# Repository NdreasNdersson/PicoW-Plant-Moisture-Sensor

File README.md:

# Install pre-commit
```
pip install pre-commit
pre-commit install
```

# Build
Following script will build the bootloader and rest sensor board application and combine these as a .bin file. It will
also prepend hash to application so it will be launched by the bootloader.
```
./build_and_combine.sh
```

# Flash first time
Connect Pico Probe and run ./flash_combined.sh

This will flash bootloader, default app info/storage and app.

# Config
Enter wifi SSID and password over serial when promted. Once it have connected, the sensors can be configured with REST API.
```
POST /SENSORS HTTP/1.1
Host: 192.168.X.X
Content-Type: application/json
Content-Length: 147

{"config":[{"calibrate_max_value":false,"calibrate_min_value":false,"inversed":true,"max":17736,"min":8266,"pin":1,"type":"moisture"},{"calibrate_max_value":false,"calibrate_min_value":true,"inversed":true,"max":16509,"min":1,"pin":2,"type":"moisture"}]}
```

# Rest get
Get sensor readings:
```
GET /SENSORS HTTP/1.1
Host: 192.168.50.205
```

Get current sensor config:
```
GET /CONFIG HTTP/1.1
Host: 192.168.50.205
```

# SW download
Run
```
./python/upload_new_binary.py --host 192.168.X.X --app-file build/ninja-release/PICO_REST_SENSOR_STRIPPED.bin
```

# Raspberry Pi Pico W Analog sensor board

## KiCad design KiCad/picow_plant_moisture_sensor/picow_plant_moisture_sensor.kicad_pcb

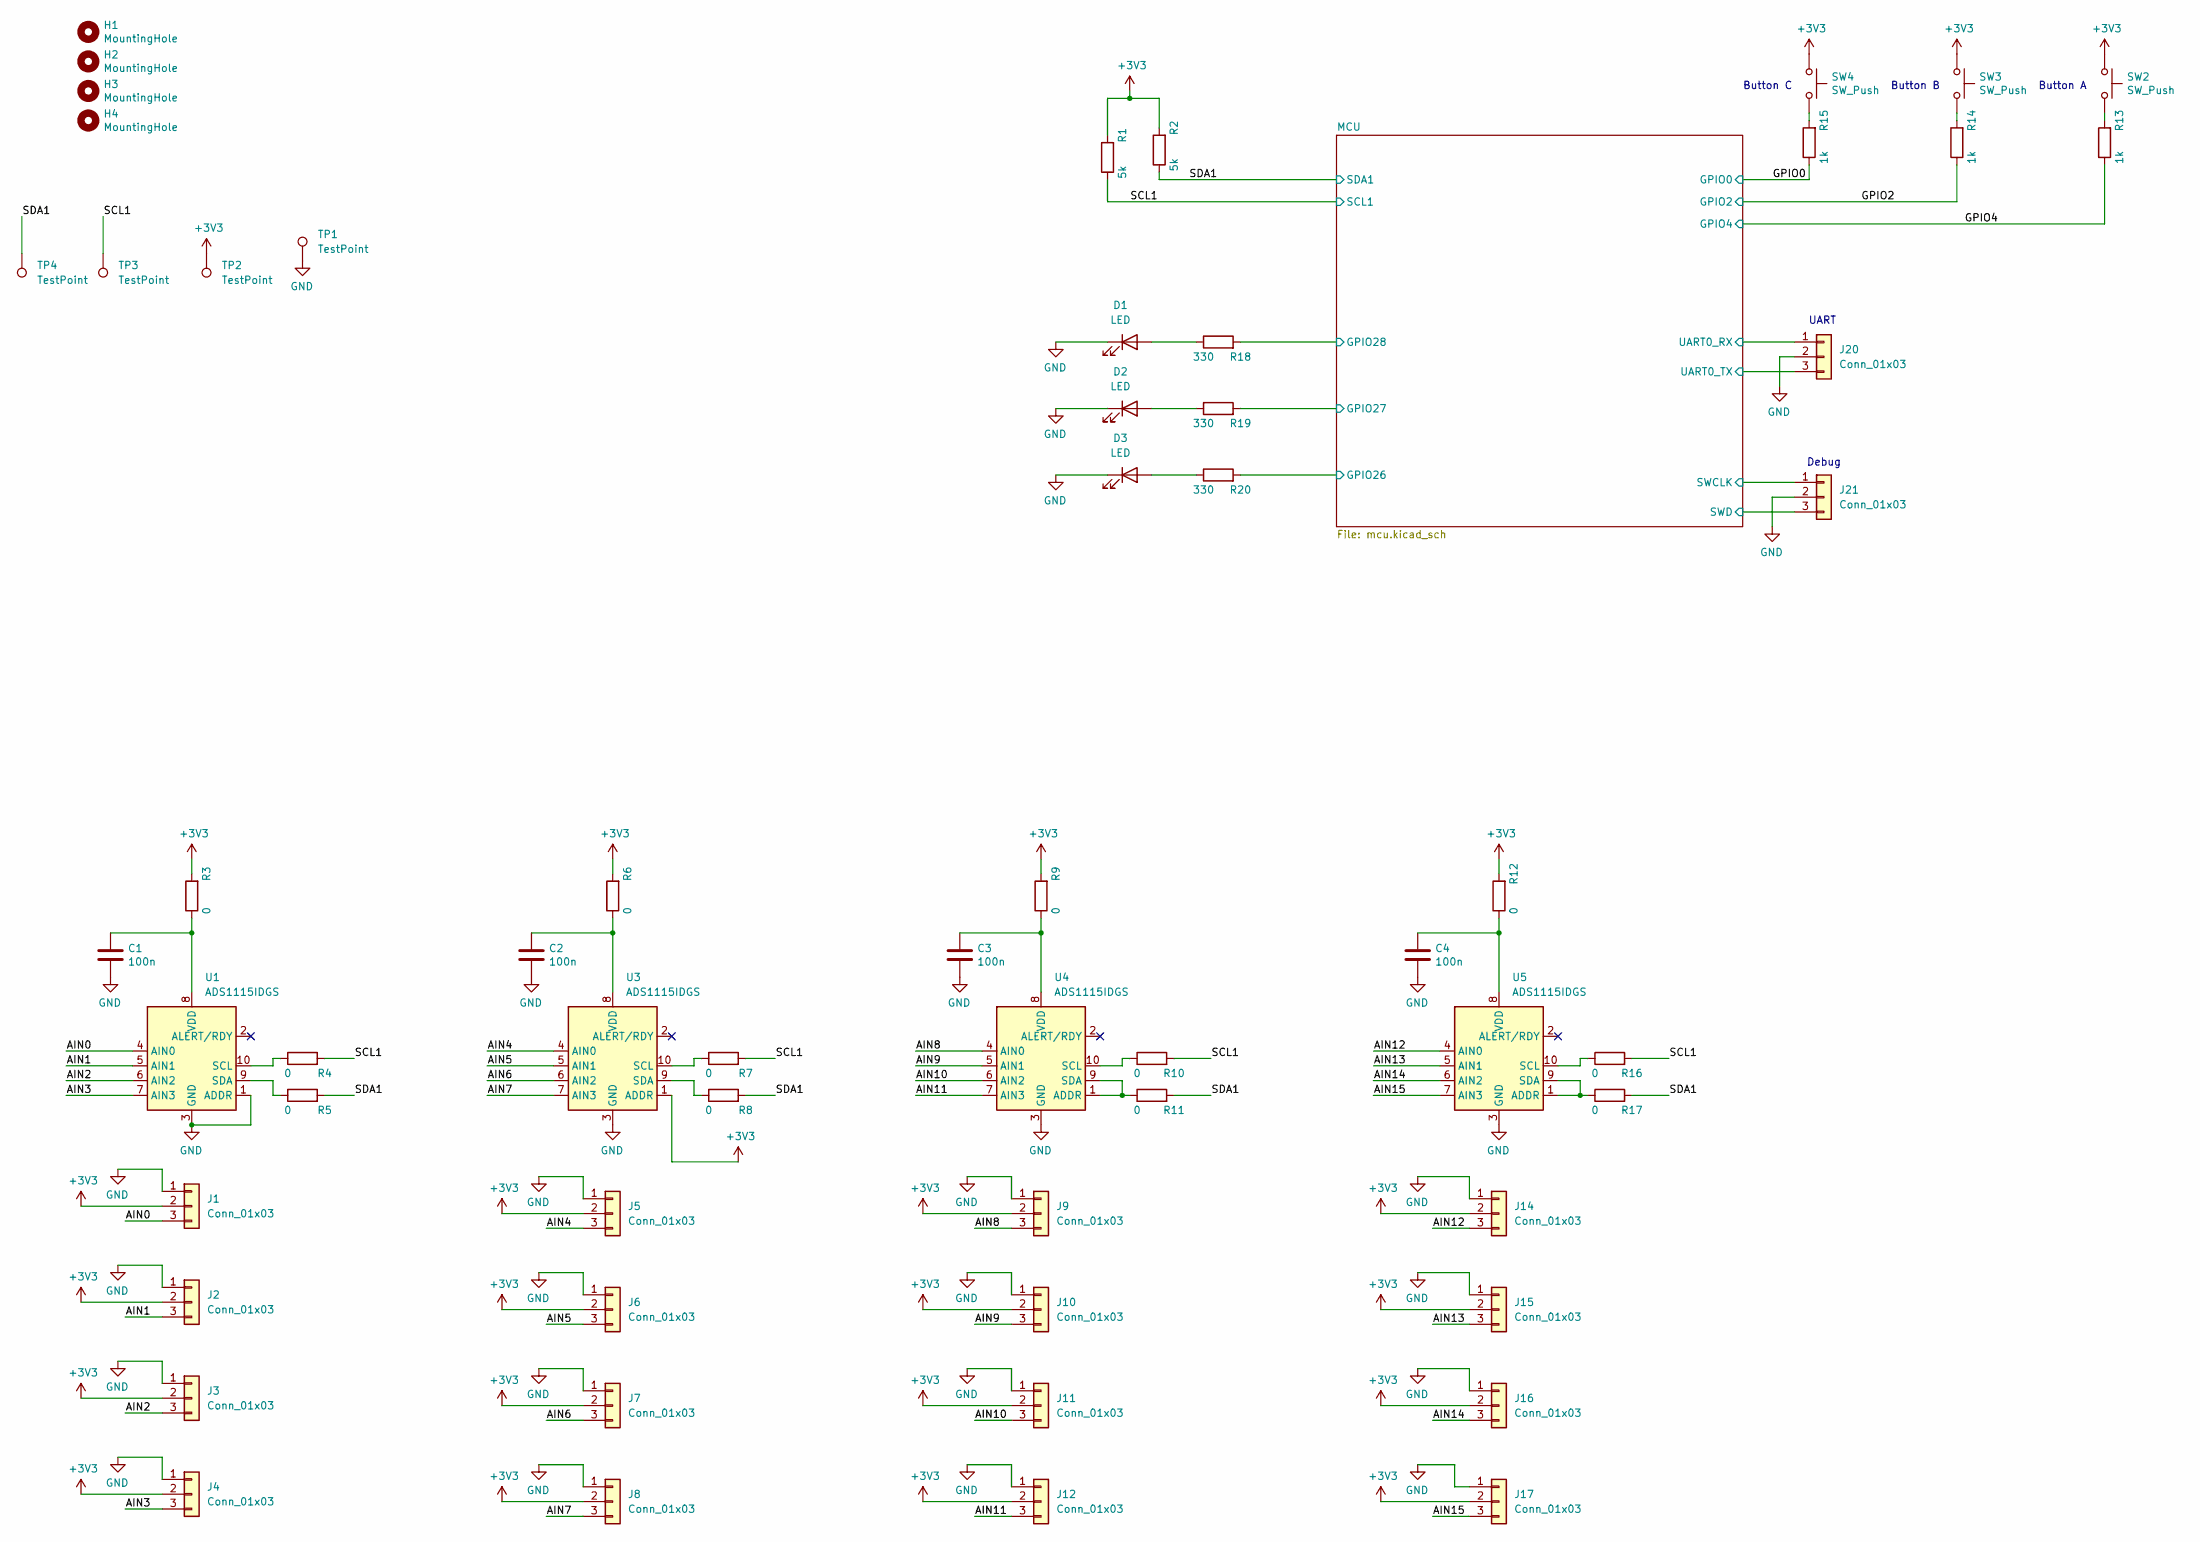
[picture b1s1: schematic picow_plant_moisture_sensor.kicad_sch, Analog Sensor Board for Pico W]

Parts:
C1, C2, C3, C4: 100n; C_0603_1608Metric; LCSC C1525
D1, D2, D3: LED; LED_0603_1608Metric; LCSC C2290
H1, H2, H3, H4: MountingHole; MountingHole_2.7mm_M2.5
J1, J2, J3, J4, J5, J6, J7, J8, J9, J10, J11, J12, J14, J15, J16, J17: Conn_01x03; JST_PH_B3B-PH-K_1x03_P2.00mm_Vertical
J20: Conn_01x03; PinHeader_1x03_P2.54mm_Vertical
J21: Conn_01x03; PinSocket_1x03_P2.54mm_Vertical
R1, R2: 5k; R_0603_1608Metric; LCSC C25900
R3, R4, R5, R6, R7, R8, R9, R10, R11, R12, R16, R17: 0; R_0603_1608Metric; LCSC C21189
R13, R14, R15: 1k; R_0603_1608Metric; LCSC C11702
R18, R19, R20: 330; R_0603_1608Metric; LCSC C25104
SW2, SW3, SW4: SW_Push; SW_SPST_TL3305A
TP1, TP2, TP3, TP4: TestPoint; TestPoint_Pad_D2.0mm
U1, U3, U4, U5: ADS1115IDGS; TSSOP-10_3x3mm_P0.5mm; LCSC C37593

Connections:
+3V3: J1.2, J2.2, J3.2, J4.2, J5.2, J6.2, J7.2, J8.2, J9.2, J10.2, J11.2, J12.2, J14.2, J15.2, J16.2, J17.2, R1.2, R2.2, R3.2, R6.2, R9.2, R12.2, SW2.1, SW3.1, SW4.1, TP2.1, U3.1 (ADDR); also elsewhere on the board
/AIN0: J1.3, U1.4 (AIN0)
/AIN1: J2.3, U1.5 (AIN1)
/AIN2: J3.3, U1.6 (AIN2)
/AIN3: J4.3, U1.7 (AIN3)
/AIN4: J5.3, U3.4 (AIN0)
/AIN5: J6.3, U3.5 (AIN1)
/AIN6: J7.3, U3.6 (AIN2)
/AIN7: J8.3, U3.7 (AIN3)
/AIN8: J9.3, U4.4 (AIN0)
/AIN9: J10.3, U4.5 (AIN1)
/AIN10: J11.3, U4.6 (AIN2)
/AIN11: J12.3, U4.7 (AIN3)
/AIN12: J14.3, U5.4 (AIN0)
/AIN13: J15.3, U5.5 (AIN1)
/AIN14: J16.3, U5.6 (AIN2)
/AIN15: J17.3, U5.7 (AIN3)
/GPIO0: R15.1; also elsewhere on the board
/GPIO2: R14.1; also elsewhere on the board
/GPIO4: R13.1; also elsewhere on the board
/MCU/GPIO26: R20.2; also elsewhere on the board
/MCU/GPIO27: R19.2; also elsewhere on the board
/MCU/GPIO28: R18.2; also elsewhere on the board
/MCU/SWCLK: J21.1; also elsewhere on the board
/MCU/SWD: J21.3; also elsewhere on the board
/MCU/UART0_RX: J20.1; also elsewhere on the board
/MCU/UART0_TX: J20.3; also elsewhere on the board
/SCL1: R1.1, R4.2, R7.2, R10.2, R16.2, TP3.1; also elsewhere on the board
/SDA1: R2.1, R5.2, R8.2, R11.2, R17.2, TP4.1; also elsewhere on the board
GND: C1.2, C2.2, C3.2, C4.2, D1.1 (K), D2.1 (K), D3.1 (K), J1.1, J2.1, J3.1, J4.1, J5.1, J6.1, J7.1, J8.1, J9.1, J10.1, J11.1, J12.1, J14.1, J15.1, J16.1, J17.1, J20.2, J21.2, TP1.1, U1.1 (ADDR), U1.3 (GND), U3.3 (GND), U4.3 (GND), U5.3 (GND); also elsewhere on the board
unnamed: D1.2 (A), R18.1
unnamed: D2.2 (A), R19.1
unnamed: D3.2 (A), R20.1
unnamed: R13.2, SW2.2
unnamed: R14.2, SW3.2
unnamed: R15.2, SW4.2
unnamed: R4.1, U1.10 (SCL)
unnamed: R5.1, U1.9 (SDA)
unnamed: C1.1, R3.1, U1.8 (VDD)
unnamed: R7.1, U3.10 (SCL)
unnamed: R8.1, U3.9 (SDA)
unnamed: C2.1, R6.1, U3.8 (VDD)
unnamed: R11.1, U4.1 (ADDR), U4.9 (SDA)
unnamed: R10.1, U4.10 (SCL)
unnamed: C3.1, R9.1, U4.8 (VDD)
unnamed: R17.1, U5.1 (ADDR), U5.9 (SDA)
unnamed: R16.1, U5.10 (SCL)
unnamed: C4.1, R12.1, U5.8 (VDD)

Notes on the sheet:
Button A
Button B
Button C
UART
Debug

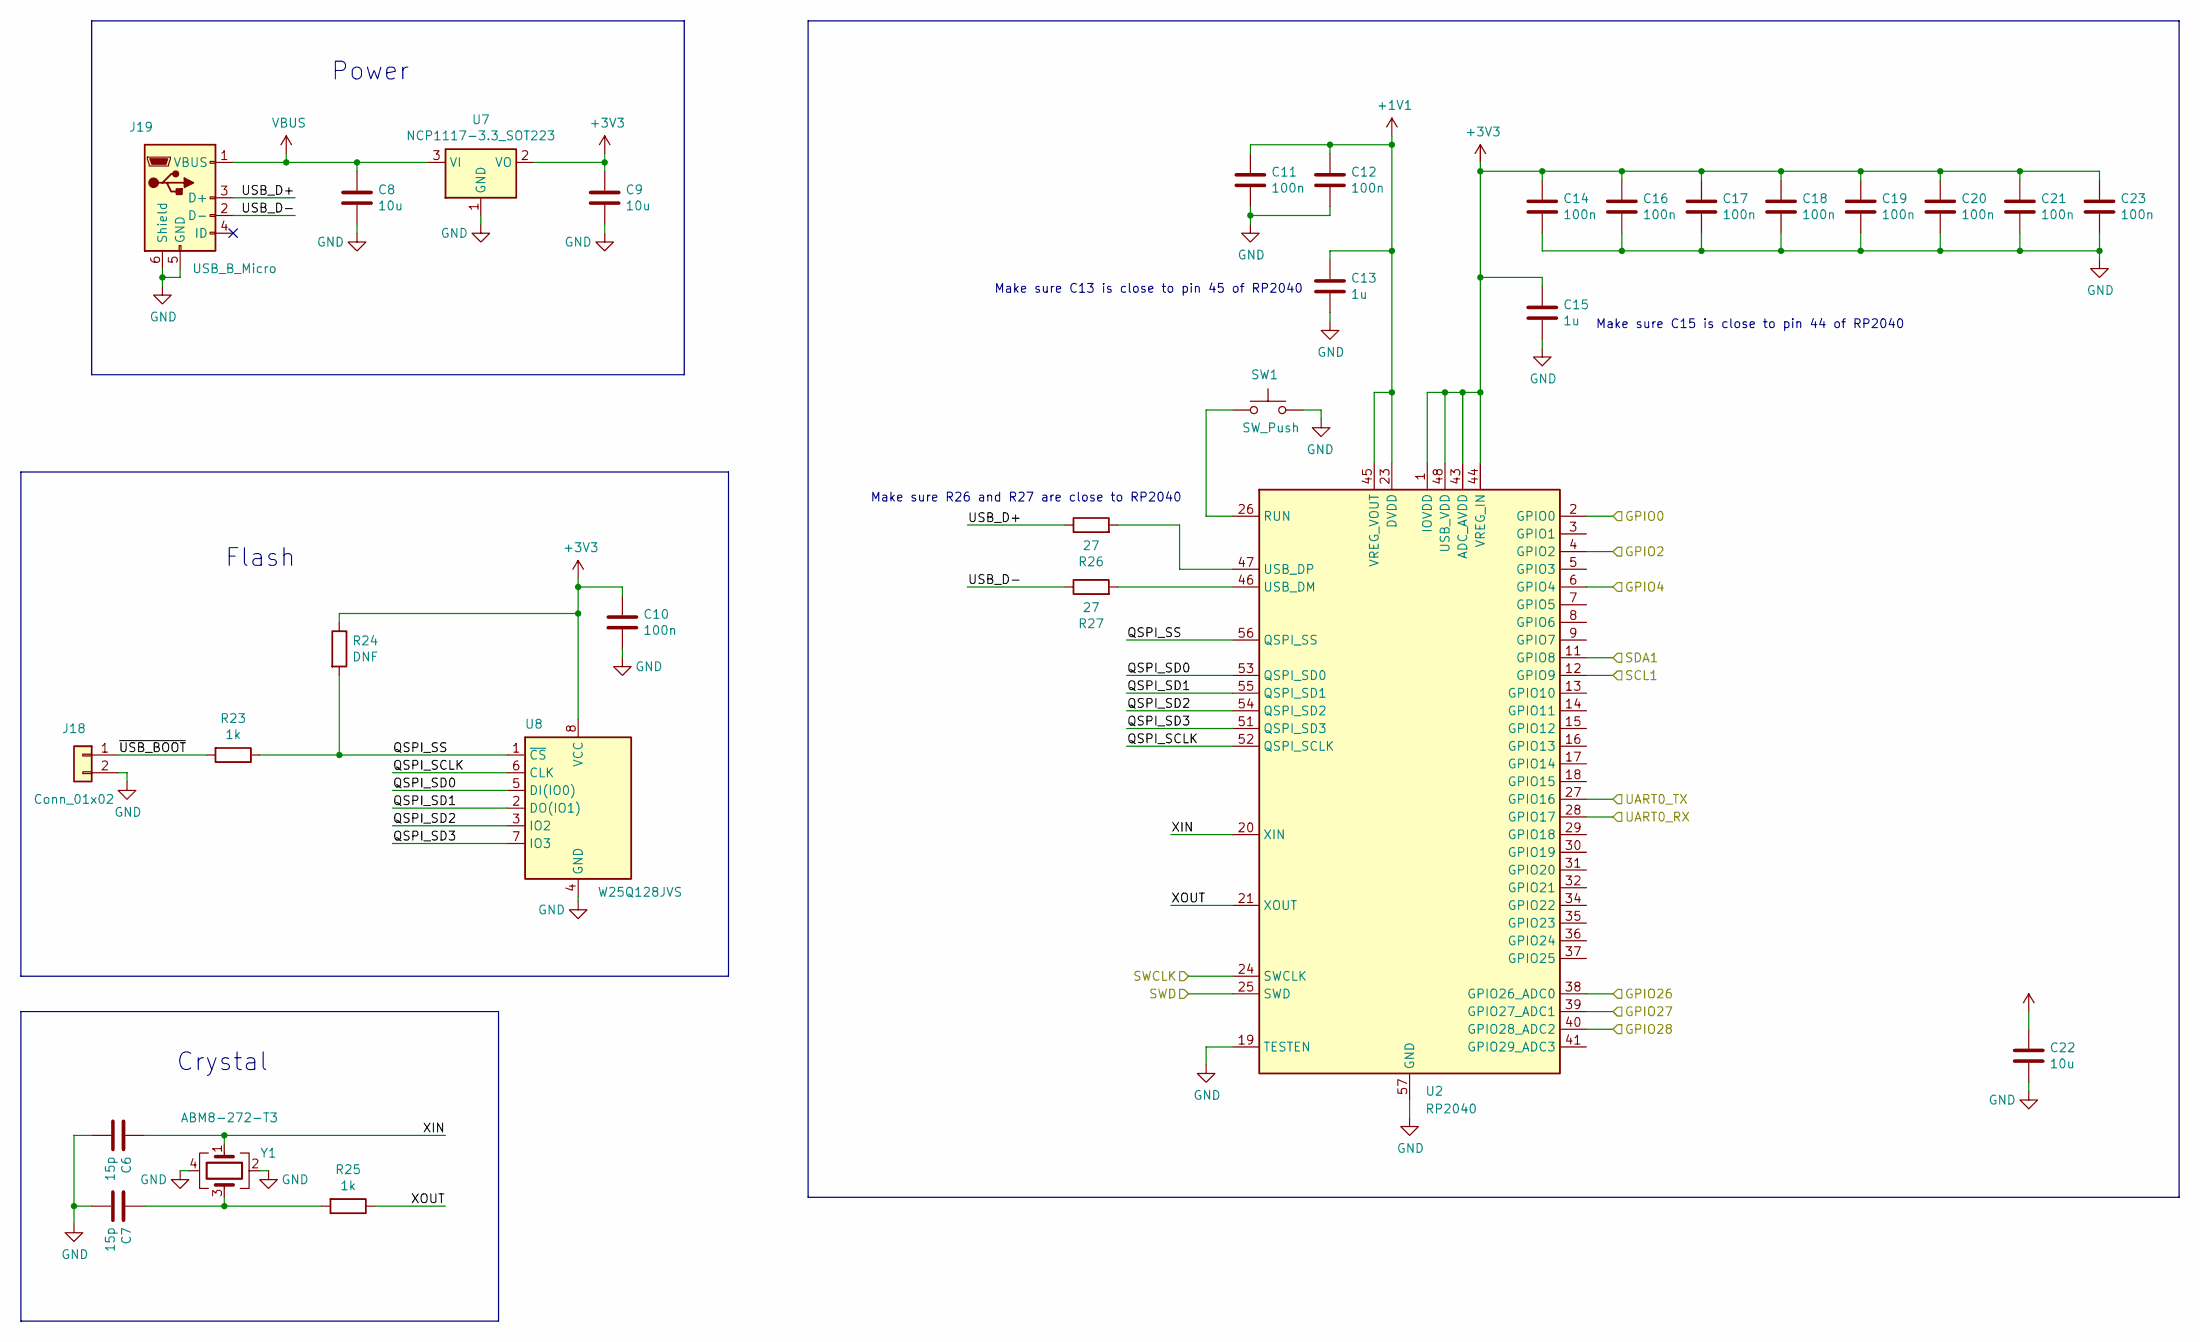
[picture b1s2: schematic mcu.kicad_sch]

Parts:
C6, C7: 15p; C_0402_1005Metric
C8, C9, C22: 10u; C_0805_2012Metric
C10, C11, C12, C14, C16, C17, C18, C19, C20, C21, C23: 100n; C_0402_1005Metric
C13, C15: 1u; C_0402_1005Metric
J18: Conn_01x02; PinHeader_1x02_P2.54mm_Vertical
J19: USB_B_Micro; USB_Micro-B_Amphenol_10103594-0001LF_Horizontal
R23, R25: 1k; R_0402_1005Metric
R24: DNF; R_0402_1005Metric
R26, R27: 27; R_0402_1005Metric
SW1: SW_Push; SW_SPST_TL3305A
U2: RP2040; QFN-56-1EP_7x7mm_P0.4mm_EP3.2x3.2mm
U7: NCP1117-3.3_SOT223; SOT-223-3_TabPin2
U8: W25Q128JVS; SOIC-8_5.23x5.23mm_P1.27mm
Y1: ABM8-272-T3; Crystal_SMD_3225-4Pin_3.2x2.5mm

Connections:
+1V1: C11.1, C12.1, C13.1, U2.23 (DVDD), U2.45 (VREG_VOUT), U2.50 (DVDD)
+3V3: C9.1, C10.1, C14.1, C15.1, C16.1, C17.1, C18.1, C19.1, C20.1, C21.1, C22.1, C23.1, R24.1, U2.1 (IOVDD), U2.10 (IOVDD), U2.22 (IOVDD), U2.33 (IOVDD), U2.42 (IOVDD), U2.43 (ADC_AVDD), U2.44 (VREG_IN), U2.48 (USB_VDD), U2.49 (IOVDD), U7.2 (VO), U8.8 (VCC); also elsewhere on the board
/GPIO0: U2.2 (GPIO0); also elsewhere on the board
/GPIO2: U2.4 (GPIO2); also elsewhere on the board
/GPIO4: U2.6 (GPIO4); also elsewhere on the board
/MCU/GPIO26: U2.38 (GPIO26_ADC0); also elsewhere on the board
/MCU/GPIO27: U2.39 (GPIO27_ADC1); also elsewhere on the board
/MCU/GPIO28: U2.40 (GPIO28_ADC2); also elsewhere on the board
/MCU/QSPI_SCLK: U2.52 (QSPI_SCLK), U8.6 (CLK)
/MCU/QSPI_SD0: U2.53 (QSPI_SD0), U8.5 (DI(IO0))
/MCU/QSPI_SD1: U2.55 (QSPI_SD1), U8.2 (DO(IO1))
/MCU/QSPI_SD2: U2.54 (QSPI_SD2), U8.3 (IO2)
/MCU/QSPI_SD3: U2.51 (QSPI_SD3), U8.7 (IO3)
/MCU/QSPI_SS: R23.1, R24.2, U2.56 (QSPI_SS), U8.1 (~CS)
/MCU/SWCLK: U2.24 (SWCLK); also elsewhere on the board
/MCU/SWD: U2.25 (SWD); also elsewhere on the board
/MCU/UART0_RX: U2.28 (GPIO17); also elsewhere on the board
/MCU/UART0_TX: U2.27 (GPIO16); also elsewhere on the board
/MCU/USB_D+: J19.3 (D+), R26.1
/MCU/USB_D-: J19.2 (D-), R27.1
/MCU/XIN: C6.1, U2.20 (XIN), Y1.1
/MCU/XOUT: R25.1, U2.21 (XOUT)
/MCU/~USB_BOOT: J18.1, R23.2
/SCL1: U2.12 (GPIO9); also elsewhere on the board
/SDA1: U2.11 (GPIO8); also elsewhere on the board
GND: C6.2, C7.2, C8.2, C9.2, C10.2, C11.2, C12.2, C13.2, C14.2, C15.2, C16.2, C17.2, C18.2, C19.2, C20.2, C21.2, C22.2, C23.2, J18.2, J19.5 (GND), J19.6 (Shield), SW1.2, U2.19 (TESTEN), U2.57 (GND), U7.1 (GND), U8.4 (GND), Y1.2, Y1.4; also elsewhere on the board
unnamed: C7.1, R25.2, Y1.3
unnamed: SW1.1, U2.26 (RUN)
unnamed: R27.2, U2.46 (USB_DM)
unnamed: R26.2, U2.47 (USB_DP)
VBUS: C8.1, J19.1 (VBUS), U7.3 (VI)

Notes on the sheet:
Make sure R26 and R27 are close to RP2040
Make sure C13 is close to pin 45 of RP2040
Power
Make sure C15 is close to pin 44 of RP2040
Flash
Crystal

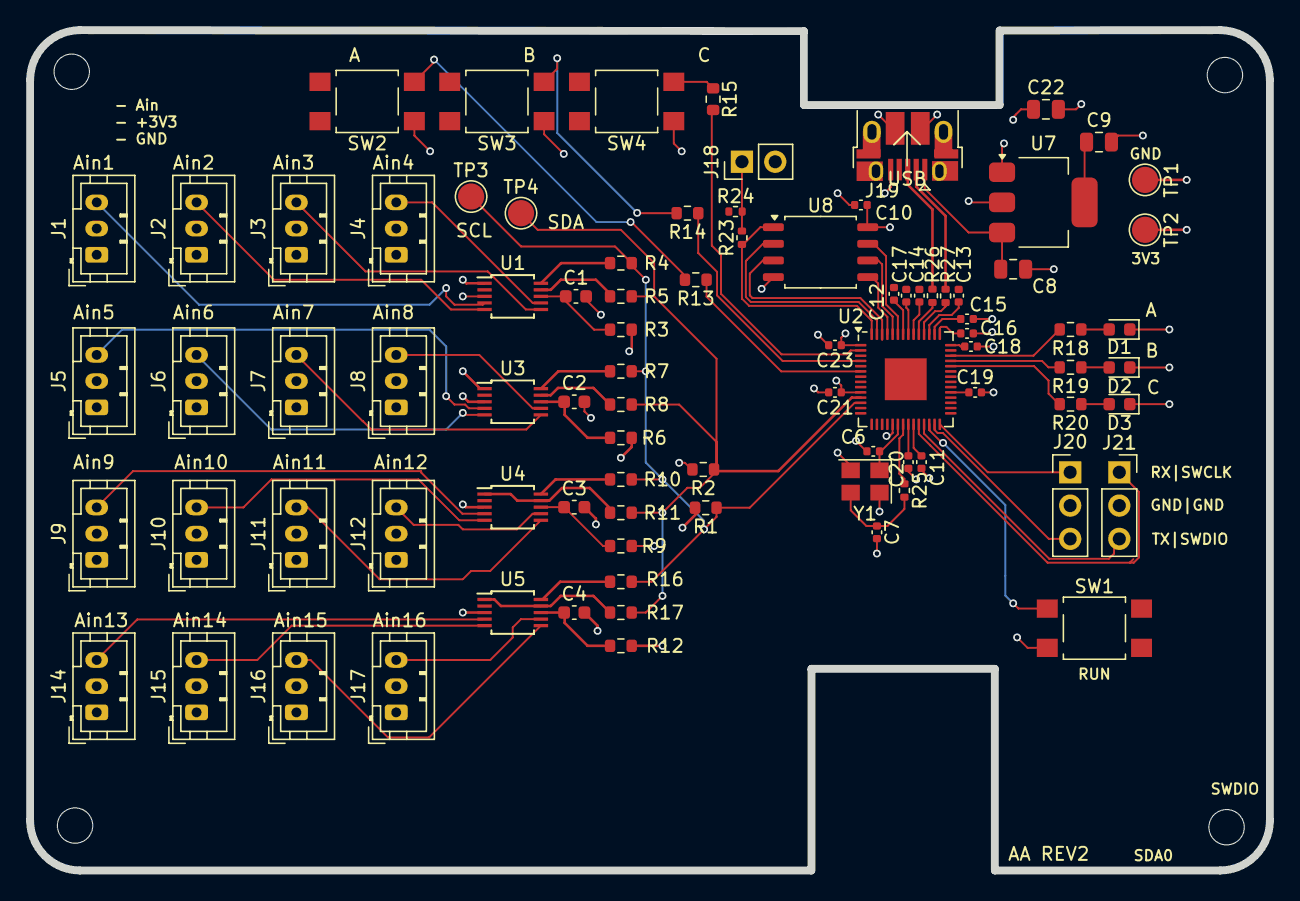
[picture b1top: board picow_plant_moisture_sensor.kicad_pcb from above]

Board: 4 copper layers, 94.6 x 64.1 mm, 90 parts (0 on the bottom side), 65 nets.

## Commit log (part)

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2024-02-03 Restructure files into folders
2024-02-04 Remove TwinThingPicoW include
2024-02-04 Logging with FreeRTOS log interface
2024-02-04 Hangs at MQTT_Connect:2710
2024-02-04 Update MQTT config
2024-02-04 Clean up of things no longer necessary
2024-02-05 TCP working with one buffer to send
2024-02-07 Sending data works
2024-02-07 Rest api (#2)
    * Restructure files into folders
    * Remove TwinThingPicoW include
    * Logging with FreeRTOS log interface
    * Hangs at MQTT_Connect:2710
    * Update MQTT config
    * Clean up of things no longer necessary
2024-02-07 Auto format all files in src
2024-02-07 Add pre-commit
2024-02-07 Run environment in CI
2024-02-07 Try .env file
2024-02-07 Change .env
2024-02-08 Add export and PWD as prefix en paths
2024-02-08 Run environment in CI (#1)
    * Run environment in CI
    * Try .env file
    * Add Dotenv Action
    * Change .env
    * Update cmake-single-platform.yml
    * Update cmake-single-platform.yml
2024-02-08 Add formatting (#2)
    * Auto format all files in src
    * Add pre-commit
2024-02-08 Upload artifact after build
2024-02-08 Upload artifact after build (#6)
2024-02-08 Reading sensor works
2024-02-09 Indent 4
2024-02-09 Add workflow to run pre-commit
2024-02-09 Add more checks and exclude configs folder
2024-02-09 Fix failing files
2024-02-09 Update formatting (#8)
    * Add ads1115 submodule
    * Reading sensor works
    * Indent 4
    * Add workflow to run pre-commit
    * Add more checks and exclude configs folder
    * Fix failing files
2024-02-09 .gitignore
2024-02-09 Set address on sda1115 devices
2024-02-09 Fix compilation warning
2024-02-09 Added skeleton of sensors
2024-02-09 First version done
2024-02-10 V1 done
2024-02-10 No traces
2024-02-10 Routing done
2024-02-12 Complete PCB design with component references
2024-02-13 Rev1 ordered
2024-02-13 10 pcb design with ics instead of complete pcb on headers (#11)
    * No traces
    * Routing done
    * Complete PCB design with component references
    * Rev1 ordered
2024-02-16 Variable number of sensors can be constructed
2024-02-17 Json can be parsed
2024-02-17 Use debug logging when build for debug
2024-02-18 Write and read from flash works
2024-02-18 A bit of clean up
2024-02-18 Back from .env, abs path not working
2024-02-18 Remove creds files
2024-02-18 Add run script
2024-02-18 Use json-maker
2024-02-19 Use json-maker (#20)
2024-02-19 Added mutex
2024-02-19 Added mutex (#24)
2024-02-19 Add proper close of main task and report on LED
2024-02-19 Use logger in tcp_server
2024-02-19 3 queded logging (#25)
    * Add proper close of main task and report on LED
    * Logging uses queue
    * Use logger in tcp_server
2024-02-24 Led Control works
2024-02-24 Led Control added (#26)
2024-02-24 Calibration routine added
2024-02-25 Calibration can be set in factory
2024-02-25 Some clean up
2024-02-26 Fix includes
2024-02-26 21 store sensor calibrations in flash (#29)
    * Calibration routine added
    * Calibration can be set in factory
    * Some clean up
    * Change json module and construct sensors based on flash config
    * Fix includes
2024-03-01 Updated FreeRTOS Kernel
2024-03-01 Update FreeRTOS Kernel (#30)
2024-03-02 Run on one core to write config
2024-03-02 Run on one core to write config (#31)
2024-03-02 Add rev2 (#33)
2024-03-03 Add eeprom cap and I2C test points
2024-03-03 32 board bring up (#35)
    * Add rev2
    * Add eeprom cap and I2C test points
2024-03-03 Exclude KiCad folder from pre-commit
2024-03-03 32 board bring up (#36)
    * Add rev2
    * Add eeprom cap and I2C test points
    * Exclude KiCad folder from pre-commit
2024-03-03 Add json serializer/deserializer
2024-03-10 Change name
2024-03-10 Implement safe write to flash
2024-03-10 Run pre-commit
2024-03-10 Fix wrong name
2024-03-11 Check flash_safe_execute return status
2024-03-11 16 disable other core when writing to flash (#40)
    * Change name
    * Implement safe write to flash
    * Run pre-commit
    * Fix wrong name
    * Check flash_safe_execute return status
2024-03-15 Post req saved to buffer
2024-03-18 Set config in flash from RestAPI
2024-03-18 Remove commented row
2024-03-18 23 implement set and get restapi (#42)
    * Get Post identified
    * Post req saved to buffer
    * Set config in flash from RestAPI
    * Remove commented row
2024-03-19 Place configs in its own headers
2024-03-21 Possible to read and write 4 pages
2024-03-23 Add compile-commands link
2024-03-24 Add compile flags and .clang-tidy
2024-04-01 Allow partial config update
2024-04-01 Handle dac out of range
2024-04-01 Turn led b on when client is connected
2024-04-01 Do not force flash
2024-04-01 Allow partial config update (#46)
    * Allow partial config update
    * Handle dac out of range
    * Turn led b on when client is connected
    * Do not force flash
    * Removed unused sent callback
2024-04-03 Remove print that overflow the print buffer
2024-04-03 Add .clangd file
2024-04-04 49 fix long string in flash not parsed properly (#50)
    * Remove print that overflow the print buffer
    * Add .clangd file
2024-04-04 Add delay to allow conversion to complete before reading
2024-04-04 Remove old ads1115 repo
2024-04-06 Button control added as publisher
2024-04-06 Button control added as publisher (#52)
    * Button control added as publisher
    * Fix includes
2024-04-07 Calibration started from button press
2024-04-07 Remove callbacks and return sensor instances instead
2024-04-07 Update logging
2024-04-07 Save calibrated values to flash
2024-04-07 47 trigger sensor calibration with button (#53)
    * Calibration started from button press
    * Remove callbacks and return sensor instances instead
    * Update logging
    * Save calibrated values to flash
    * Show readings and calibration on led A
2024-04-12 Raw value sent
2024-04-12 Add low pass filter
2024-04-12 54 send both calculated and raw value (#55)
    * Raw value sent
    * Add low pass filter
2024-04-12 Add option to retrive config
2024-04-12 Add option to retrive config (#56)
2024-04-13 Change to filter for float
2024-04-13 Add config and script to run
2024-04-14 Fixed warnings in utils button/led and logging stack
2024-04-14 Use default constructor and initialize all members
2024-04-14 Auto fix all files
2024-04-14 Add more checks
2024-04-18 18 add clang tidy (#59)
    * Add config and script to run
    * Fixed warnings in utils button/led and logging stack
    * Use default constructor and initialize all members
    * Auto fix all files
    * Add more checks
2024-04-18 Clangtidy auto fix
2024-04-18 Change struct names
2024-04-18 Clang tidy fixes (#62)
    * Fix clang-tidy suggestions
    * Clangtidy auto fix
    * Change struct names
2024-09-03 Add bootloader repo and integrate
2024-09-03 Link bootloader lib and use correct flash storage area
2024-09-03 Request wifi config over serial if already not saved
2024-09-04 Use more restrictive wildcards for artifacts
2024-09-04 SWDL working
2024-09-04 Auto format all files
2024-09-04 65 add bootloader an swdw (#66)
    * Add bootloader repo and integrate
    * Link bootloader lib and use correct flash storage area
    * Request wifi config over serial if already not saved
    * Send hash and app size to SWDW
    * Use more restrictive wildcards for artifacts
    * SWDL working
2024-09-05 Use post callback instead of receive buffer
2024-09-05 Allow full blocks of download data
2024-09-06 Move bootloader to libs
2024-09-06 Reply ok after command is processed (#69)
    * Use post callback instead of receive buffer
    * Allow full blocks of download data
    * Both GET methods working
    * Update readme
    * Move bootloader to libs
2024-09-06 Restart if sensor config was updated
2024-09-06 Restart if sensor config was updated (#71)
2024-09-09 Design with RP2040 IC instead of pico board
2024-09-09 Remove run clang-tidy
2024-09-10 Fix static code analysis warnings
2024-09-10 Remove __ from names and update include guards
2024-09-10 Remove newline in logger
2024-09-10 Upgrade FreeRTOS
2024-09-10 Increase logger thread stack
2024-09-10 Build release by default
2024-09-10 Update bootloader lib
2024-09-10 73 try codechecker (#74)
    * Remove run clang-tidy
    * CodeChecker auto fix
    * Fix static code analysis warnings
    * Remove __ from names and update include guards
    * Fix static code analysis warnings
    * Remove newline in logger
2024-09-11 Use interface type Sensor
2024-09-11 Add internal temperature as a sensor
2024-09-11 75 create generic sensor implementation (#76)
    * Use interface type Sensor
    * Add internal temperature as a sensor
2024-09-12 Remove first OK response
2024-09-13 Clean up files
2024-09-13 Build with docker
2024-09-13 Run docker command
2024-09-13 Use pico-sdk and freertos kernel from env
2024-09-13 Use docker for all github action commands
2024-09-13 CodeChecker run without error
2024-09-16 Fail only if parse fails, not on warnings
2024-09-16 Fix static code analysis warning
2024-09-16 Define app storage globally
2024-09-17 Increase tcp stack size
2024-09-17 Print c style string
2024-09-17 Use docker to build (#80)
    * Clean up files
    * Build with docker
    * Run docker command
    * Use pico-sdk and freertos kernel from env
    * Use docker for all github action commands
    * CodeChecker run without error
2024-09-17 Remove logger (#82)
2024-09-17 Unsubscribe at destruction
2024-09-17 Always initialize temp sensor
2024-09-17 Fix static code analyzis warnings
2024-09-17 Unsubscribe at destruction (#84)
    * Unsubscribe at destruction
    * Always initialize temp sensor
    * Fix static code analyzis warnings
2024-09-17 Use payload for publisher and subscribers notify
2024-09-18 Sensors use publisher api
2024-09-18 85 add sensor subscription (#86)
    * Use payload for publisher and subscribers notify
    * Sensors use publisher api
    * Restructure get config content
    * Fix static code analysis warnings
    * Delete copy constructors and so on
2024-09-18 Move main code to its own class
2024-09-18 Add callback to restore when button B is pressed
2024-09-19 Instantiate button control later, otherwise interupts don't work
2024-09-19 Start task after interupts
2024-09-19 Update with newest bootloader
2024-09-26 Update to newest bootloader
2024-09-26 Fix run unittests
2024-09-26 Do not track compile_commands
2024-09-26 Update to newest bootloader (#90)
    * Update to newest bootloader
    * Fix run unittests
    * Do not track compile_commands
2024-09-26 Update (#93)
2024-09-27 Add pico interface files
2024-09-30 Align with changes for unittests
2024-09-30 Run config handler init
2024-10-01 Update bootloader
2024-10-01 Add config handler interface and align pico bootloader namespace
2024-10-02 Mock FreeRTOS and software download
2024-10-03 Test get and post
2024-12-23 Sensors build with Bazel
2024-12-23 Build with Bazel on github
2024-12-23 Add aliases to docker bashrc
2024-12-23 Do not use alias in build command
2024-12-23 Build Bazel without docker
2025-01-18 Update build.yml (#98)
2025-01-20 Trigger calibration from updated sensor config
2025-01-20 99 remote start of calibration (#101)
    * Add calibration config
    * Trigger calibration from updated sensor config
    * Update readme
2025-01-21 Add test for new json structure
2025-01-21 94 add unittests (#95)
    * Add pico interface files
    * Add test for config handler
    * Align with changes for unittests
    * Run config handler init
    * Update bootloader
    * Add config handler interface and align pico bootloader namespace
2025-01-21 Upload uf2 file
2025-01-21 Upload uf2 file (#103)
2025-01-21 Use correct start address (#105)
2025-01-26 Add MQTT client and config handling
2025-01-26 Add REST MQTT post handler
2025-01-26 Move all configs to config handler folder
2025-01-26 Update tests
